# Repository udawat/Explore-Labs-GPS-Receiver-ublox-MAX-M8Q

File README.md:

# Explore Labs GPS Receiver - ublox MAX-M8Q

<p>The Global Positioning System (GPS) is a satellite-based navigation system made up of a network of 24 or more satellites. Explore Labs GPS Receiver is a 72-channel device based on the uBlox 8th generation chipset that captures those signals and provides accurate location and time information. It has an operating voltage of 3.3V to 5.5V, a high quality ceramic patch antenna on board, and connects to your system via TTL serial broken out on 2.54 cm breadboard compatible pads.</p>

<p><strong>Design Features:</strong></p>
<ul>
    <li>Upto 18 Hz update rate for GPS-only mode.</li>
    <li>40 square mm Ground Plane for better antenna gain and directivity.</li>
    <li>External I2C EEPROM for receiver configuration storage</li>
    <li>Backup battery as Supercapacitor for efficient warm start and storage of settings. Currently provides backup time of approx 10 seconds.</li>
    <li>Power Input: 3.3V to 5.5V Input. Or, If connected to an IMU 9 DOF AHRS, may be powered by a Single-cell Lithium Polymer battery.</li>
    <li>1 TTL UART port @ 3.3V. Use a Logic Level converter in between if using a 5V device like an Arduino Uno.</li>
    <li>Power LED - Red and 1PPS Timepulse LED - Blue</li>
    <li>JST-SH six pin horizontal connector - 1.0mm pitch (EM-406, EM-506 compatibile).</li>
    <li>Dimensions: 40 mm x 40 mm x 8.5 mm</li>
    <li>Weight: 16 gram</li>
    <li>Fully assembled and ready to use.</li>
    <li>Supports direct connection with <a title="Explore Labs IMU 9 DOF AHRS With Pressure / Altitude / Humidity / Temperature Sensor" href="https://github.com/udawat/IMU-9DoF-AHRS" target="_blank">Explore Labs IMU 9 DOF AHRS</a>.</li>
    <li>Code library: <a title="Tiny GPS" href="http://github.com/mikalhart/TinyGPS/" target="_blank">TinyGPS</a>.</li>
</ul>

<p><strong>Technical Specifications:</strong></p>
<ul>
    <li>72-channel u-blox M8 engine</li>
    <li>Tracking & Navigation Sensitivity for GPS & GLONASS: –167 dBm</li>
    <li>Horizontal position accuracy: 2.5m CEP</li>
    <li>Time-To-First-Fix for GPS & GLONASS (Cold Start) : 26s (Open Sky)</li>
    <li>Maximum Navigation Update Rate:
        <ul>
            <li>For GPS & GLONASS: 10Hz</li>
            <li>For GPS only: 18Hz</li>
        </ul>
    </li>
</ul>

<p><strong>Applications:</strong></p>
<ul>
    <li>Can be used in UAVs or Hot Air Balloon (HAB) projects.</li>
    <li>Can be used for evaluating the ublox MAX positioning module.</li>
    <li>Vehicle Tracking System and as Fleet Management for Logistics.</li>
    <li>Geocaching - Treasure Hunt.</li>
</ul>

<p><strong>Documents:</strong></p>
<ul>
    <li>Data Sheet: <a title="u-blox MAX-M8" href="https://www.u-blox.com/sites/default/files/MAX-M8_DataSheet_%28UBX-13004644%29.pdf" target="_blank">u-blox MAX-M8</a></li>
</ul>

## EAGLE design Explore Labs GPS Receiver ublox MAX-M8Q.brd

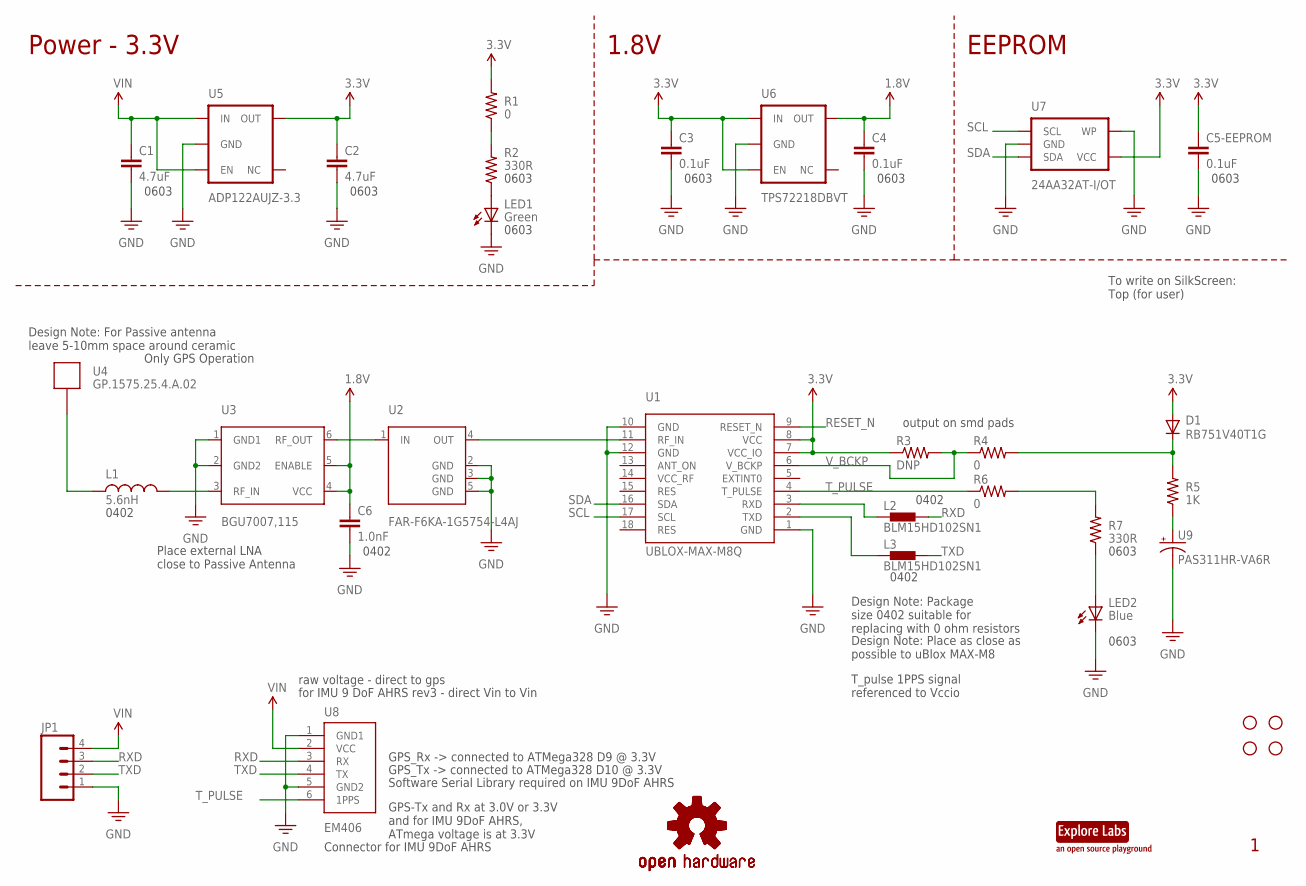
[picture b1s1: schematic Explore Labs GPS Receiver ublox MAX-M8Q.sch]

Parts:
C1, C2: 4.7uF; 0603-CAP
C3, C4, C5-EEPROM: 0.1uF; 0603-CAP
C6: 1.0nF; 0402-CAP
D1: RB751V40T1G; SOD-323
JP1: M04PTH; 1X04
L1: 5.6nH; C0402
L2, L3: BLM15HD102SN1; 0402-FERRITE
LED1: Green; CHIP-LED0603
LED2: Blue; CHIP-LED0603
LOGO1: OSHW-LOGOTOP; OSHW-LOGO-M-TOP
LOGO2: OSHW-LOGOBOTTOM; OSHW-LOGO-M-BOTTOM
R1, R4, R6: 0; 0603-RES
R2, R7: 330R; 0603-RES
R3: DNP; 0603-RES
R5: 1K; 0603-RES
STANDOFF1, STANDOFF2, STANDOFF3, STANDOFF4: STAND-OFF
U1: UBLOX-MAX-M8Q; UBLOX-MAX-M8
U2: FAR-F6KA-1G5754-L4AJ; QCS5E
U3: BGU7007,115; SOT886
U4: GP.1575.25.4.A.02
U5: ADP122AUJZ-3.3; SOT-23-5
U6: TPS72218DBVT; SOT-23-5
U7: 24AA32AT-I/OT; SOT-23-5
U8: EM406
U9: PAS311HR-VA6R; PA311
U$9: EXPLORE-LABS-LOGO; EXPLORE-LABS-LOGO-TOP

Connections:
1.8V: C4.1, C6.1, U3.4 (VCC), U3.5 (ENABLE), U6.5 (OUT)
3.3V: C2.1, C3.1, C5-EEPROM.1, D1.2 (A), R1.2, R3.1, U1.7 (VCC_IO), U1.8 (VCC), U5.5 (OUT), U6.1 (IN), U6.3 (EN), U7.4 (VCC)
GND: C1.2, C2.2, C3.2, C4.2, C5-EEPROM.2, C6.2, JP1.1, LED1.C, LED2.C, U1.1 (GND), U1.10 (GND), U1.12 (GND), U2.2 (GND), U2.3 (GND), U2.5 (GND), U3.1 (GND1), U3.2 (GND2), U5.2 (GND), U6.2 (GND), U7.2 (GND), U7.5 (WP), U8.1 (GND1), U8.5 (GND2), U9.P$2 (-)
unnamed: U2.1 (IN), U3.6 (RF_OUT)
unnamed: R5.1, U9.P$1 (+)
unnamed: L2.1, U1.3 (RXD)
unnamed: R6.2, R7.2
unnamed: LED2.A, R7.1
unnamed: L3.1, U1.2 (TXD)
unnamed: U1.11 (RF_IN), U2.4 (OUT)
unnamed: D1.1 (C), R4.2, R5.2
unnamed: L1.2, U3.3 (RF_IN)
unnamed: R1.1, R2.2
unnamed: L1.1, U4.1
unnamed: LED1.A, R2.1
RESET_N: U1.9 (RESET_N)
RXD: JP1.3, L2.2, U8.3 (RX)
SCL: U1.17 (SCL), U7.1 (SCL)
SDA: U1.16 (SDA), U7.3 (SDA)
TXD: JP1.2, L3.2, U8.4 (TX)
T_PULSE: R6.1, U1.4 (T_PULSE), U8.6 (1PPS)
VIN: C1.1, JP1.4, U5.1 (IN), U5.3 (EN), U8.2 (VCC)
V_BCKP: R3.2, R4.1, U1.6 (V_BCKP)

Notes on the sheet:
Power - 3.3V
raw voltage - direct to gps
for IMU 9 DoF AHRS rev3 - direct Vin to Vin
Design Note: Place as close as possible to uBlox MAX-M8
Design Note: For Passive antenna leave 5-10mm space around ceramic
GPS-Tx and Rx at 3.0V or 3.3V and for IMU 9DoF AHRS, ATmega voltage is at 3.3V
output on smd pads
Only GPS Operation
Place external LNA close to Passive Antenna
Connector for IMU 9DoF AHRS
GPS_Tx -> connected to ATMega328 D10 @ 3.3V
GPS_Rx -> connected to ATMega328 D9 @ 3.3V
Software Serial Library required on IMU 9DoF AHRS
0603
Design Note: Package size 0402 suitable for replacing with 0 ohm resistors
0402
1.8V
EEPROM
To write on SilkScreen: Top (for user)
T_pulse 1PPS signal referenced to Vccio

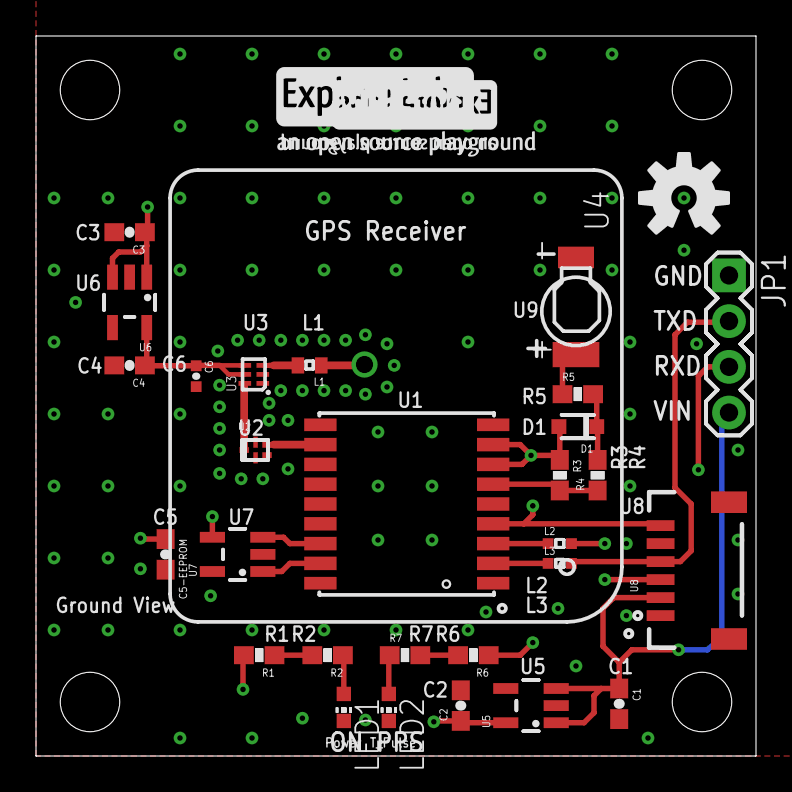
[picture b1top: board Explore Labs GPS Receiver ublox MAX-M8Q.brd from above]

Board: 4 copper layers, 40.0 x 40.0 mm, 37 parts (1 on the bottom side), 22 nets.

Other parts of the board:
U$10: EXLABS_LOGO_0.25

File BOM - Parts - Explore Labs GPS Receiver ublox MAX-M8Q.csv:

"Part";"Value";"Device";"Package";"Description";"DATASHEET";"LINK";"MFGPN";"PROD_ID";"VALUE";
"C1";"4.7uF";"CAP0603-CAP";"0603-CAP";"Capacitor";"";"";"";"";"";
"C2";"4.7uF";"CAP0603-CAP";"0603-CAP";"Capacitor";"";"";"";"";"";
"C3";"0.1uF";"CAP0603-CAP";"0603-CAP";"Capacitor";"";"";"";"";"";
"C4";"0.1uF";"CAP0603-CAP";"0603-CAP";"Capacitor";"";"";"";"";"";
"C5-EEPROM";"0.1uF";"CAP0603-CAP";"0603-CAP";"Capacitor";"";"";"";"";"";
"C6";"1.0nF";"1.0UF-16V-10%(0402)";"0402-CAP";"";"";"";"";"CAP-12417";"1.0uF";
"D1";"RB751V40T1G";"DIODESOD";"SOD-323";"Diode";"";"";"";"DIO-09646";"";
"JP1";"";"M04PTH";"1X04";"Header 4";"";"";"";"";"";
"L1";"5.6nH";"INDUCTOR0402";"C0402";"Inductors";"";"";"";"";"";
"L2";"BLM15HD102SN1";"BLM15HD102SN1";"0402-FERRITE";"EMIFIL (R) Chip Ferrite Bead for GHz Noise";"";"";"";"";"";
"L3";"BLM15HD102SN1";"BLM15HD102SN1";"0402-FERRITE";"EMIFIL (R) Chip Ferrite Bead for GHz Noise";"";"";"";"";"";
"LED1";"Green";"LEDCHIP-LED0603";"CHIP-LED0603";"LED";"";"";"";"";"";
"LED2";"Blue";"LEDCHIP-LED0603";"CHIP-LED0603";"LED";"";"";"";"";"";
"LOGO1";"OSHW-LOGOTOP";"OSHW-LOGOTOP";"OSHW-LOGO-M-TOP";"Open Source Hardware Logo This logo indicates the piece of hardware it is found on incorporates a OSHW license and/or adheres to the definition of open source hardware found here: http://freedomdefined.org/OSHW";"";"";"";"";"";
"LOGO2";"OSHW-LOGOBOTTOM";"OSHW-LOGOBOTTOM";"OSHW-LOGO-M-BOTTOM";"Open Source Hardware Logo This logo indicates the piece of hardware it is found on incorporates a OSHW license and/or adheres to the definition of open source hardware found here: http://freedomdefined.org/OSHW";"";"";"";"";"";
"R1";"0";"RESISTOR0603-RES";"0603-RES";"Resistor";"";"";"";"";"";
"R2";"330R";"RESISTOR0603-RES";"0603-RES";"Resistor";"";"";"";"";"";
"R3";"DNP";"RESISTOR0603-RES";"0603-RES";"Resistor";"";"";"";"";"";
"R4";"0";"RESISTOR0603-RES";"0603-RES";"Resistor";"";"";"";"";"";
"R5";"1K";"RESISTOR0603-RES";"0603-RES";"Resistor";"";"";"";"";"";
"R6";"0";"RESISTOR0603-RES";"0603-RES";"Resistor";"";"";"";"";"";
"R7";"330R";"RESISTOR0603-RES";"0603-RES";"Resistor";"";"";"";"";"";
"STANDOFF1";"STAND-OFF";"STAND-OFF";"STAND-OFF";"#4 Stand Off";"";"";"";"";"";
"STANDOFF2";"STAND-OFF";"STAND-OFF";"STAND-OFF";"#4 Stand Off";"";"";"";"";"";
"STANDOFF3";"STAND-OFF";"STAND-OFF";"STAND-OFF";"#4 Stand Off";"";"";"";"";"";
"STANDOFF4";"STAND-OFF";"STAND-OFF";"STAND-OFF";"#4 Stand Off";"";"";"";"";"";
"U$9";"EXPLORE-LABS-LOGO";"EXPLORE-LABS-LOGO";"EXPLORE-LABS-LOGO-TOP";"";"";"";"";"";"";
"U1";"UBLOX-MAX-M8Q";"UBLOX-MAX-M8Q";"UBLOX-MAX-M8";"";"";"";"";"";"";
"U2";"FAR-F6KA-1G5754-L4AJ";"FAR-F6KA-1G5754-L4AJ";"QCS5E";"";"";"";"";"";"";
"U3";"BGU7007,115";"BGU7007,115";"SOT886";"";"";"";"";"";"";
"U4";"GP.1575.25.4.A.02";"GP.1575.25.4.A.02";"GP.1575.25.4.A.02";"Taoglas GP.1575.25.4.A.02 4mm thick GPS Patch Antenna, 1575MHz";"http://www.taoglas.com/images/product_images/original_images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";"http://www.taoglas.com/antennas/GPS-GLONASS_Antennas/Interna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";"GP.1575.25.4.A.02";"";"";
"U5";"ADP122AUJZ-3.3";"ADP122AUJZ-3.3";"SOT-23-5";"";"";"";"";"";"";
"U6";"TPS72218DBVT";"TPS72218DBVT";"SOT-23-5";"";"";"";"";"";"";
"U7";"24AA32AT-I/OT";"24AA32AT-I/OT";"SOT-23-5";"";"";"";"";"";"";
"U8";"EM406";"EM406";"EM406";"EM406 GPS Connector";"";"";"";"";"";
"U9";"PAS311HR-VA6R";"PAS311HR-VA6R";"PA311";"";"";"";"";"";"";

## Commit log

2016-04-19 minor edits
    Title change
2016-04-19 added schematic and board files
    Exported parts BOM in csv format. Schematic in PDF.
2016-04-19 added description
2020-05-01 links updated
2020-06-28 Set theme jekyll-theme-cayman

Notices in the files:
parts and their libraries:
SparkFun-Capacitors: Licensing: CC v3.0 Share-Alike You are welcome to use this library for commercial purposes.
SparkFun-Electromechanical: Licensing: Creative Commons ShareAlike 4.0 International - https://creativecommons.org/licenses/by-sa/4.0
11xLabs: Released under the Creative Commons
